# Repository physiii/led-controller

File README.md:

# open-led
ESP32 Based LED Controller

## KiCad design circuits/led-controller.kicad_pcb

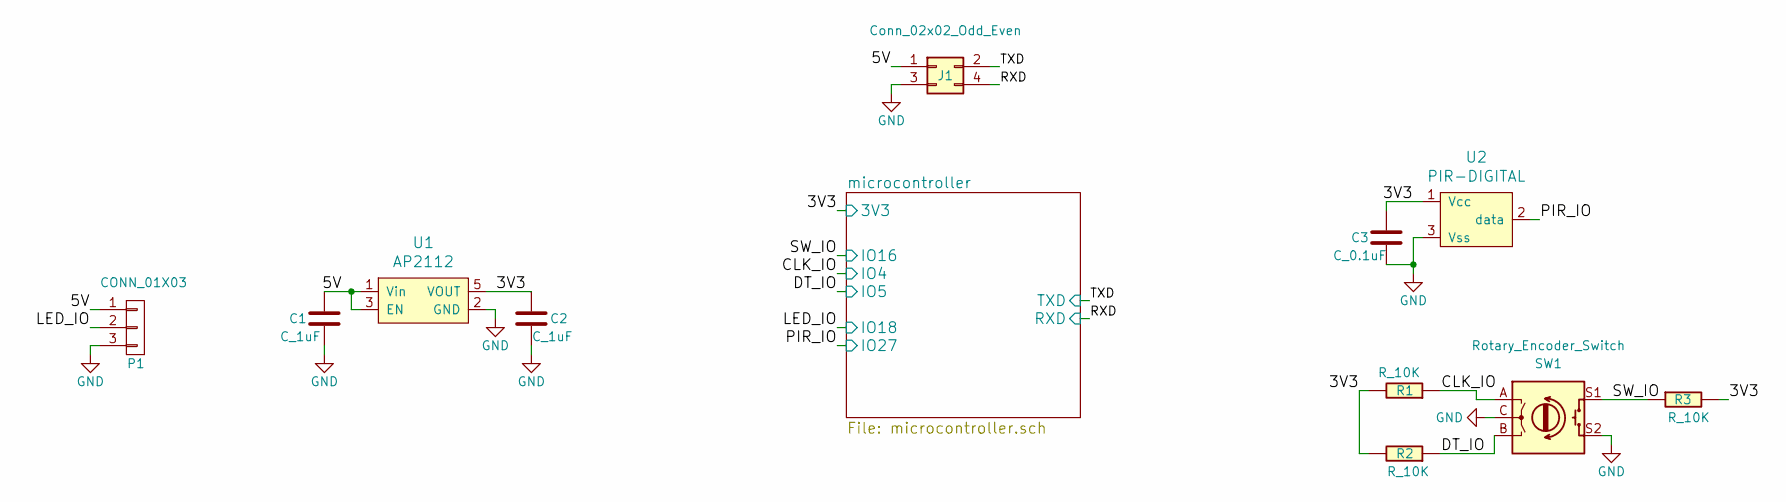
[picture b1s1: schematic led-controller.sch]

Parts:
C1, C2: C_1uF; C_0603_1608Metric_Pad1.05x0.95mm_HandSolder; Part Number GCM188R71C105KA64D
C3: C_0.1uF; C_0603_1608Metric_Pad1.05x0.95mm_HandSolder; Part Number C1608X8R1H104K080AB
J1: Conn_02x02_Odd_Even; PinHeader_2x02_P2.54mm_Vertical_SMD
P1: CONN_01X03; PinHeader_1x03_P2.54mm_Vertical
R1, R2, R3: R_10K; R_0603_1608Metric_Pad1.05x0.95mm_HandSolder; Part Number RC0603JR-0710KL
SW1: Rotary_Encoder_Switch; RotaryEncoder_Alps_EC11E-Switch_Vertical_H20mm; Part Number EC11
U1: AP2112; SOT-23-5_HandSoldering; Part Number AP2112
U2: PIR-DIGITAL; TO-5-3; Part Number PYQ2898

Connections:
/3V3: C2.1, C3.1, R1.2, R2.2, R3.2, U1.5 (VOUT), U2.1 (Vcc); also elsewhere on the board
/5V: C1.1, J1.1, P1.1, U1.1 (Vin), U1.3 (EN)
/CLK_IO: R1.1, SW1.A; also elsewhere on the board
/DT_IO: R2.1, SW1.B; also elsewhere on the board
/LED_IO: P1.2; also elsewhere on the board
/PIR_IO: U2.2 (data); also elsewhere on the board
/RXD: J1.4; also elsewhere on the board
/SW_IO: R3.1, SW1.S1; also elsewhere on the board
/TXD: J1.2; also elsewhere on the board
GND: C1.2, C2.2, C3.2, J1.3, P1.3, SW1.C, SW1.S2, U1.2 (GND), U2.3 (Vss); also elsewhere on the board

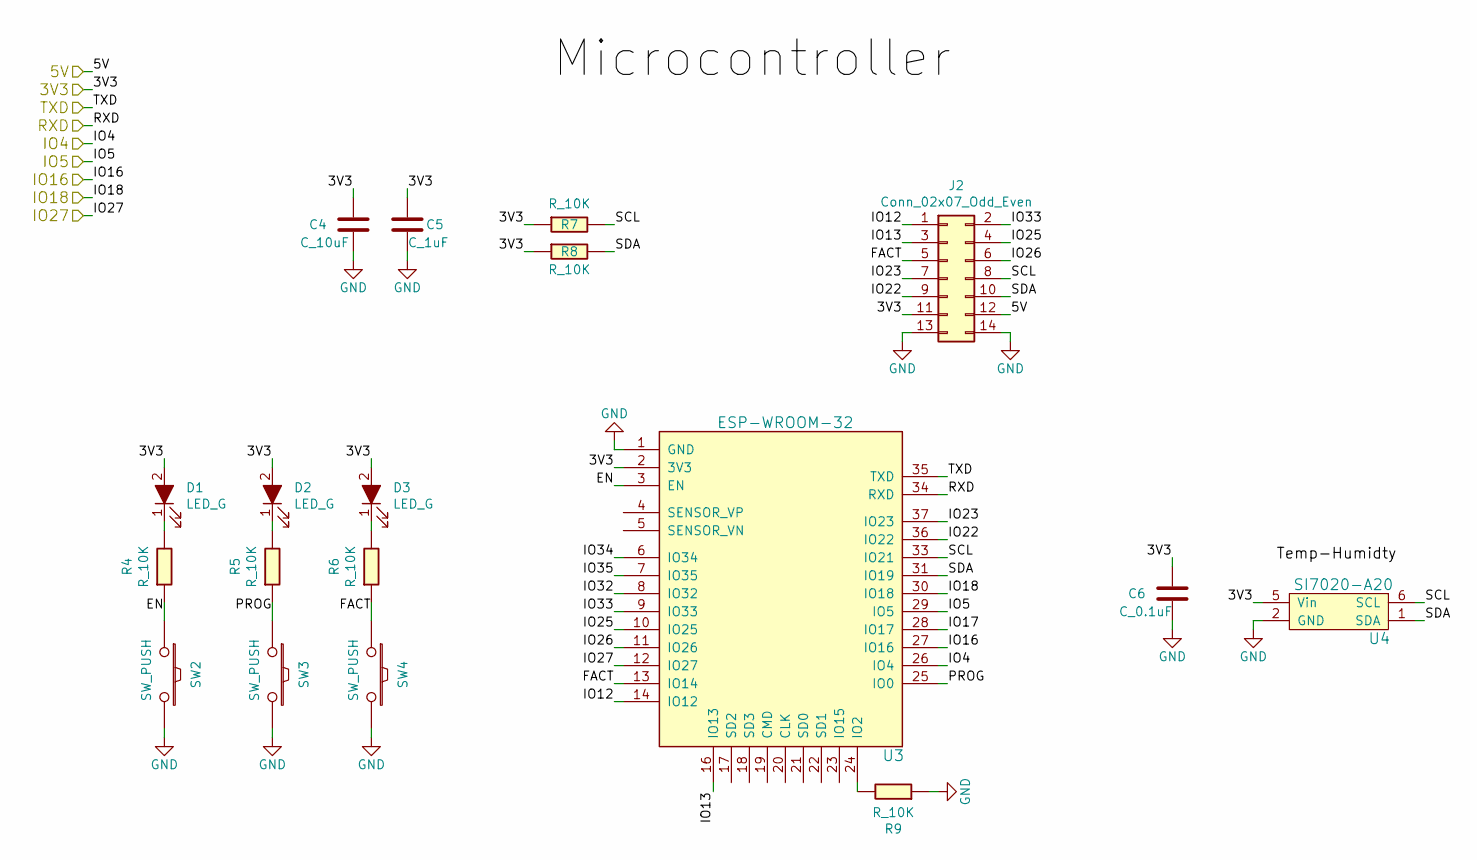
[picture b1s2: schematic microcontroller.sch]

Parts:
C4: C_10uF; C_0603_1608Metric_Pad1.05x0.95mm_HandSolder; Part Number GRM188R61E106KA73D
C5: C_1uF; C_0603_1608Metric_Pad1.05x0.95mm_HandSolder; Part Number GCM188R71C105KA64D
C6: C_0.1uF; C_0603_1608Metric_Pad1.05x0.95mm_HandSolder; Part Number C1608X8R1H104K080AB
D1, D2, D3: LED_G; D_0603_1608Metric_Pad1.05x0.95mm_HandSolder; Part Number 150060VS75000
J2: Conn_02x07_Odd_Even; PinHeader_2x07_P2.54mm_Vertical_SMD
R4, R5, R6, R7, R8, R9: R_10K; R_0603_1608Metric_Pad1.05x0.95mm_HandSolder; Part Number RC0603JR-0710KL
SW2, SW3, SW4: SW_PUSH; SW_Push_1P1T_NO_CK_KMR2; Part Number KMR211NG LFS
U3: ESP-WROOM-32; Part Number ESP-WROOM-32
U4: SI7020-A20; Part Number SI7020-A20-GM1R

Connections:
/3V3: C4.1, C5.1, C6.1, D1.2 (A), D2.2 (A), D3.2 (A), J2.11, R7.1, R8.1, U3.2 (3V3), U4.5 (Vin); also elsewhere on the board
/CLK_IO: U3.26 (IO4); also elsewhere on the board
/DT_IO: U3.29 (IO5); also elsewhere on the board
/LED_IO: U3.30 (IO18); also elsewhere on the board
/PIR_IO: U3.12 (IO27); also elsewhere on the board
/RXD: U3.34 (RXD); also elsewhere on the board
/SW_IO: U3.27 (IO16); also elsewhere on the board
/TXD: U3.35 (TXD); also elsewhere on the board
/microcontroller/5V: J2.12
/microcontroller/EN: R4.1, SW2.1, U3.3 (EN)
/microcontroller/FACT: J2.5, R6.1, SW4.1, U3.13 (IO14)
/microcontroller/IO12: J2.1, U3.14 (IO12)
/microcontroller/IO13: J2.3, U3.16 (IO13)
/microcontroller/IO17: U3.28 (IO17)
/microcontroller/IO22: J2.9, U3.36 (IO22)
/microcontroller/IO23: J2.7, U3.37 (IO23)
/microcontroller/IO25: J2.4, U3.10 (IO25)
/microcontroller/IO26: J2.6, U3.11 (IO26)
/microcontroller/IO32: U3.8 (IO32)
/microcontroller/IO33: J2.2, U3.9 (IO33)
/microcontroller/IO34: U3.6 (IO34)
/microcontroller/IO35: U3.7 (IO35)
/microcontroller/PROG: R5.1, SW3.1, U3.25 (IO0)
/microcontroller/SCL: J2.8, R7.2, U3.33 (IO21), U4.6 (SCL)
/microcontroller/SDA: J2.10, R8.2, U3.31 (IO19), U4.1 (SDA)
GND: C4.2, C5.2, C6.2, J2.13, J2.14, R9.1, SW2.2, SW3.2, SW4.2, U3.1 (GND), U4.2 (GND); also elsewhere on the board
unnamed: D1.1 (K), R4.2
unnamed: D2.1 (K), R5.2
unnamed: D3.1 (K), R6.2
unnamed: R9.2, U3.24 (IO2)

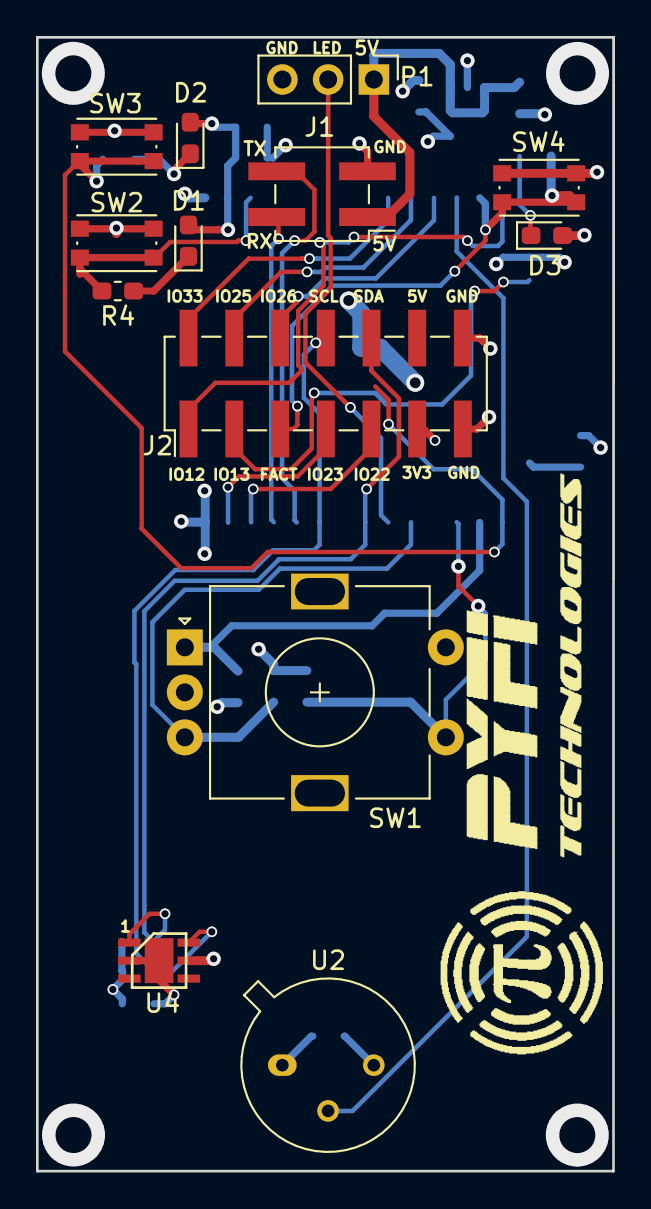
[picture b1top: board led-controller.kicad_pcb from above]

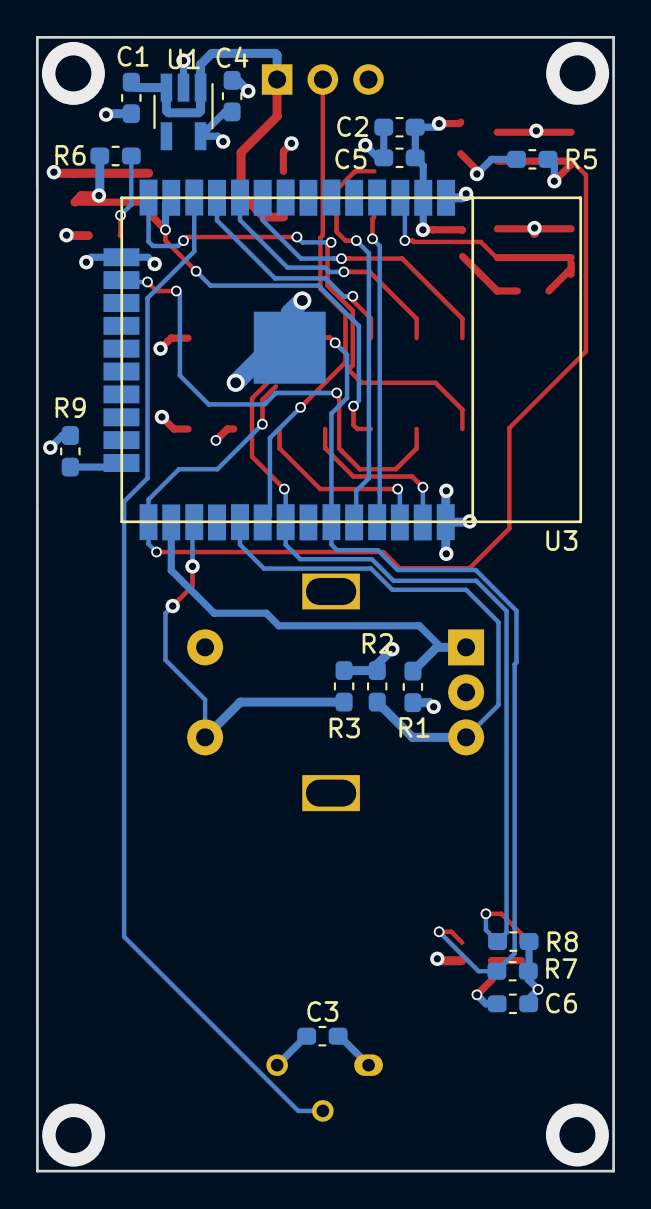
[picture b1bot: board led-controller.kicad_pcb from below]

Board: 4 copper layers, 32.0 x 63.0 mm, 30 parts (16 on the bottom side), 26 nets.

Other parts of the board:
LOGO: LOGO

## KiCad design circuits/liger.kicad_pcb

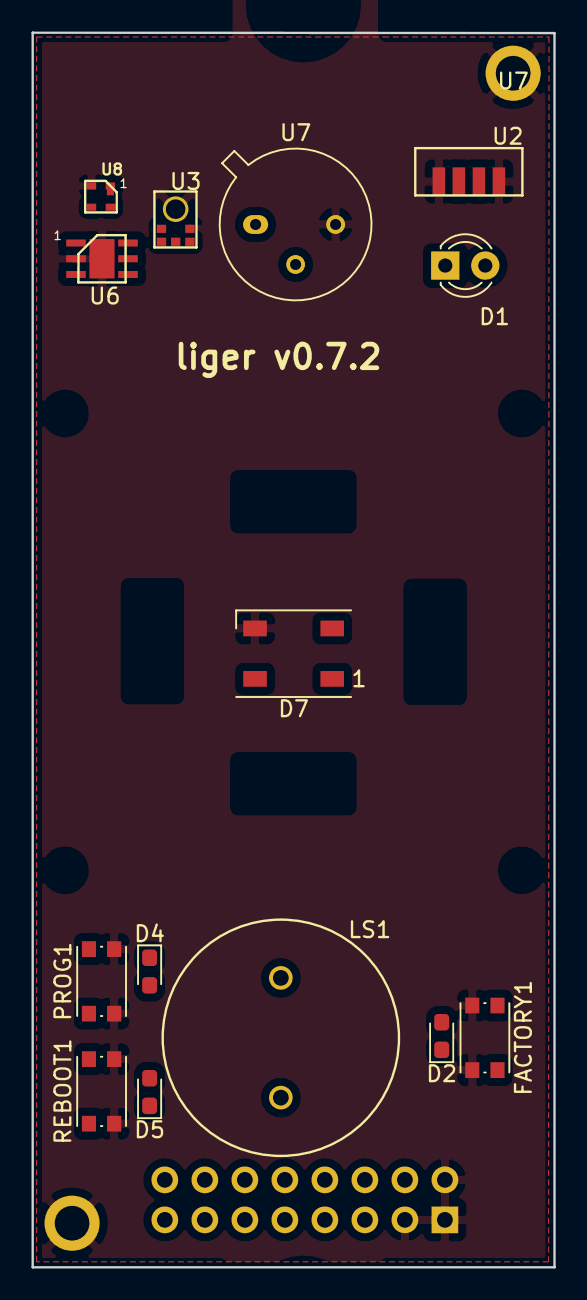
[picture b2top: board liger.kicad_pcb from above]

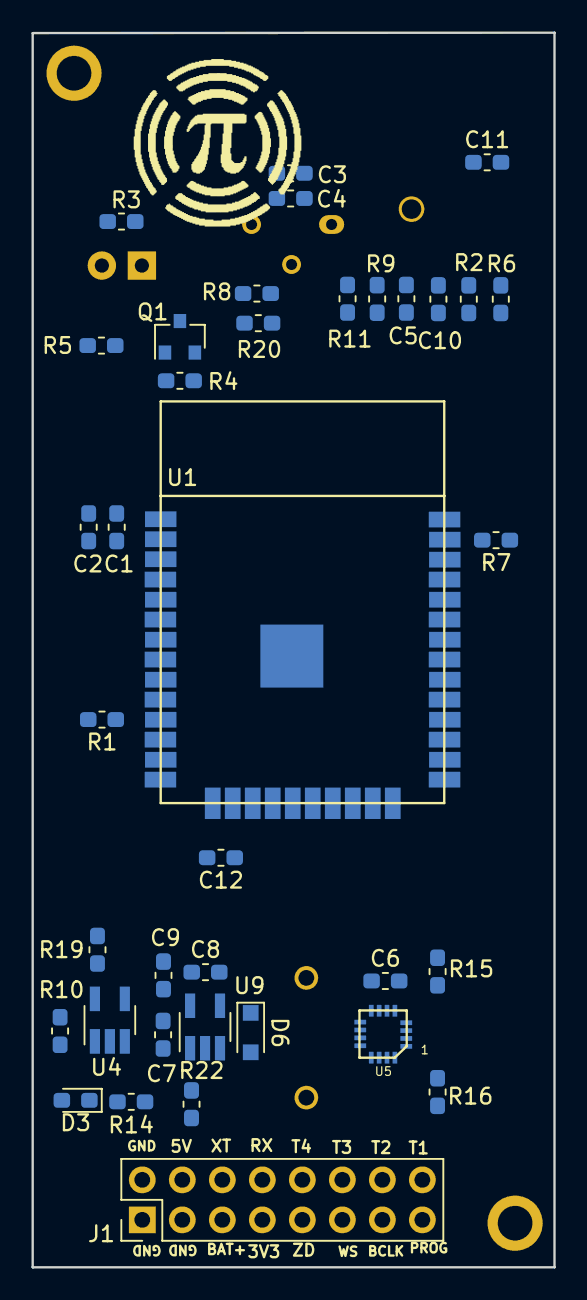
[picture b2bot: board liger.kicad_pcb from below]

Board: 4 copper layers, 33.1 x 78.4 mm, 53 parts (38 on the bottom side), 41 nets, no tracks yet.

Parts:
C1: C_10uF; C_0603_1608Metric_Pad1.05x0.95mm_HandSolder
C2, C7, C8, C9, C12: C_1uF; C_0603_1608Metric_Pad1.05x0.95mm_HandSolder
C3, C5, C6, C10, C11: C_0.1uF; C_0603_1608Metric_Pad1.05x0.95mm_HandSolder
C4: C_100pF; C_0603_1608Metric_Pad1.05x0.95mm_HandSolder
D1: LED; LED_D3.0mm
D2, D3, D4, D5: LED-0603-G; LED_0603_1608Metric_Pad1.05x0.95mm_HandSolder
D6: D_Schottky-BAT20JFILM; D_SOD-323_HandSoldering
D7: WS2812B; LED_WS2812B_PLCC4_5.0x5.0mm_P3.2mm
FACTORY1: SW_PUSH; SW_SPST_KMR2
J1: Conn_02x08_Odd_Even; PinHeader_2x08_P2.54mm_Vertical
LOGO: pyfi_symbol
LS1: speaker-CVS-1508; speaker-1508
PROG1: SW_PUSH; SW_SPST_KMR2
Q1: Q_NPN_BEC; SOT-23
R1, R7, R8, R11: R_47.5; R_0603_1608Metric_Pad1.05x0.95mm_HandSolder
R2, R6, R22: R_10k; R_0603_1608Metric_Pad1.05x0.95mm_HandSolder
R3, R4, R10, R14, R15, R16: R_1k; R_0603_1608Metric_Pad1.05x0.95mm_HandSolder
R5: 36; R_0603_1608Metric_Pad1.05x0.95mm_HandSolder
R9, R20: R_100k; R_0603_1608Metric_Pad1.05x0.95mm_HandSolder
R19: R_2k; R_0603_1608Metric_Pad1.05x0.95mm_HandSolder
REBOOT1: SW_PUSH; SW_SPST_KMR2
U1: ESP-WROOM-32
U2: IR-RX-TSOP34438; TSOP75338TR
U3: SPH0645LM4H-B
U4: MCP73831T; SOT-23-5_HandSoldering
U5: MAX98357AETE+T; MAX98357A
U6: SI7020-A20
U7: PYQ2898; TO-5-3
U7#2: housing-mounts; generic-housing-mounts-md
U8: TSL45315CL; LIGHT-SENSOR-TSL45315CL
U9: AP2112; SOT-23-5_HandSoldering

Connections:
/3V3: C1.1, C2.1, C3.1, C5.1, C8.1, C10.1, C11.1, D2.2, D4.2, D5.2, J1.7, R2.1, R5.1, R6.1, U1.2, U2.Vs, U3.5, U6.5, U7.1, U8.1, U9.5
/BUTTON_LED: D7.4, U1.30
/EN: R16.2, REBOOT1.1, U1.3
/FACTORY_RST: FACTORY1.1, R14.2, U1.13
/I2S_BCLK: J1.13, R1.2, U3.4, U5.16
/I2S_DATA_IN: R11.1, U1.36
/I2S_DATA_OUT: U1.10, U5.1
/I2S_WS: J1.11, R7.1, U3.1, U5.14
/IR_RX: R3.1, U1.27
/IR_TX: R4.2, U1.26
/PIR: R8.1, R20.2, U1.23
/PROG: J1.15, PROG1.1, R15.2, U1.25
/RELAY_1: J1.16, U1.24
/RELAY_2: J1.14, U1.29
/RELAY_3: J1.12, U1.28
/RELAY_4: J1.10, U1.6
/RXD: J1.8, U1.34
/SCL: R2.2, U1.33, U6.6, U8.4
/SDA: R6.2, U1.31, U6.1, U8.3
/TXD: J1.6, U1.35
/V_BAT: C9.1, J1.5, U4.3
/V_IN: C6.1, C7.1, C12.2, D6.1, D7.1, U5.4, U5.7, U9.1, U9.3
/V_USB: D6.2, J1.4, R10.1, R22.1, U4.4
/ZERO_DETECT: J1.9, U1.7
GND: C1.2, C2.2, C3.2, C4.2, C5.2, C6.2, C7.2, C8.2, C9.2, C10.2, C11.2, C12.1, D7.3, FACTORY1.2, J1.1, J1.2, J1.3, PROG1.2, Q1.2, R9.1, R19.1, R20.1, R22.2, REBOOT1.2, U1.1, U2.GND, U3.2, U3.3, U4.2, U5.3, U6.2, U7.3, U7#2.1, U8.2, U9.2
unnamed: C4.1, R8.2, U7.2
unnamed: D1.1, Q1.3
unnamed: D1.2, R5.2
unnamed: D2.1, R14.1
unnamed: D3.1, U4.1
unnamed: D3.2, R10.2
unnamed: D4.1, R15.1
unnamed: D5.1, R16.1
unnamed: LS1.1, U5.10
unnamed: LS1.2, U5.9
unnamed: Q1.1, R4.1
unnamed: R1.1, U1.11
unnamed: R3.2, U2.OUT
unnamed: R7.2, U1.37
unnamed: R9.2, R11.2, U3.6
unnamed: R19.2, U4.5

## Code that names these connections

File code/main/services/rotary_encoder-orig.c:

#include <stdio.h>
#include <string.h>
#include <stdlib.h>
#include "freertos/FreeRTOS.h"
#include "freertos/task.h"
#include "freertos/queue.h"
#include "driver/gpio.h"

#define NR    0 // not rotating
#define CW    1 // clock-wise rotation
#define CCW   2 // counter-clock-wise rotation
#define ESP_INTR_FLAG_DEFAULT 0

int debounce_count = 0;
int hold_thresh = 10;
int hold_cnt = 0;
int rotary_state = 0;
int prev_rotary_state = 0;
bool start_hold_cnt = false;
bool select_mode_enabled = false;

static xQueueHandle gpio_evt_queue = NULL;

struct rotary_encoder {
  int SW;
  int CLK;
  int DT;
  int SW_IO;
  int CLK_IO;
  int DT_IO;
  int rotated;
  int pressed;
  int dt_value;
  int clk_value;
  int prev_dt_value;
  long int debounce;
};

struct rotary_encoder rcA;

static void IRAM_ATTR gpio_isr_handler(void* arg)
{
    uint32_t gpio_num = (uint32_t) arg;
    // xQueueSendFromISR(gpio_evt_queue, &gpio_num, NULL);
    // Rotation event
    if (gpio_num == rcA.DT_IO) {
      rcA.clk_value = gpio_get_level(rcA.CLK_IO);
      rcA.dt_value = gpio_get_level(rcA.DT_IO);
      if (!rcA.dt_value && rcA.prev_dt_value) {
        if (rcA.clk_value) {
          rotary_state = CCW;
        } else {
          rotary_state = CW;
        }
      }
      rcA.prev_dt_value = rcA.dt_value;
    }
}

void reset_hold_count() {
  hold_cnt = 0;
}

void toggle_hold_count() {
  if (start_hold_cnt) {
    printf("double click delay: %d\n", hold_cnt);
  } else {
    hold_cnt = 0;
  }

  start_hold_cnt = !start_hold_cnt;
}

void start_hold_count()
{
  start_hold_cnt = true;
}

void stop_hold_count()
{
  start_hold_cnt = false;
}

int get_click_delay()
{
  int ret = hold_cnt;
  hold_cnt = 0;
  return ret;
}

void enter_scene_select_mode(bool mode)
{
  select_mode_enabled = mode;
  printf("Scene select mode. %d\n", select_mode_enabled);
}

static void rotary_encoder_task(void *pvParameter) {
  while (1) {

    if (rotary_state == CCW) {
      // if (prev_rotary_state != rotary_state) printf("Rotating CCW.\n");
      printf("Rotating CCW.\n");
    }

    if (rotary_state == CW) {
      // if (prev_rotary_state != rotary_state) printf("Rotating CW.\n");
      // nextMode();
      printf("Rotating CW.\n");
    }
    // prev_rotary_state = rotary_state;
    // rcA.prev_dt_value = rcA.dt_value;

    rotary_state = NR;
    vTaskDelay(10 / portTICK_PERIOD_MS);
  }
}

static void rotary_encoder_task_old(void* arg)
{
    uint32_t io_num;
    int cnt = 0;
    for(;;) {
        if(xQueueReceive(gpio_evt_queue, &io_num, portMAX_DELAY)) {
            // printf("GPIO[%d] intr, val: %d\n", io_num, gpio_get_level(io_num));
            cJSON *level_json = NULL;

            // Switch event
            if (io_num == rcA.SW_IO) {
              rcA.pressed = !gpio_get_level(rcA.SW_IO);
              if (!rcA.pressed) continue;
              if (debounce_count - rcA.debounce > 0) {
                LED_payload = cJSON_CreateObject();
                level_json = cJSON_CreateBool(true);
                cJSON_AddItemToObject(LED_payload, "toggle", level_json);
                int delay = get_click_delay();
                printf("Toggle (%d)\n", delay);
                if (delay < 5) {
                  enter_scene_select_mode(true);
                } else {
                  enter_scene_select_mode(false);
                }
                debounce_count = 0;
              }
            }

            // Rotation event
            if (io_num == rcA.DT_IO) {
              rcA.clk_value = gpio_get_level(rcA.CLK_IO);
              rcA.dt_value = gpio_get_level(rcA.DT_IO);

              if (!rcA.dt_value && rcA.prev_dt_value) {
                if (rcA.clk_value) {
                  LED_payload = cJSON_CreateObject();
                  level_json = cJSON_CreateNumber(12);
                  if (select_mode_enabled) {
                    nextMode();
                  } else {
                    cJSON_AddItemToObject(LED_payload, "decBrightness", level_json);
                  }

                  printf("CCW\n");
                } else {
                  LED_payload = cJSON_CreateObject();
                  level_json = cJSON_CreateNumber(12);
                  if (select_mode_enabled) {
                    prevMode();
                  } else {
                    cJSON_AddItemToObject(LED_payload, "incBrightness", level_json);
                  }
                  printf("CW\n");
                }
              }
              rcA.prev_dt_value = rcA.dt_value;
            }

        }
    }
}

static void debounce_task(void *pvParameter) {
  while (1) {
    debounce_count++;
    vTaskDelay(10 / portTICK_PERIOD_MS);
  }
}

static void hold_task(void *pvParameter) {
  while (1) {
    hold_cnt++;
    vTaskDelay(100 / portTICK_PERIOD_MS);
  }
}

void rotary_encoder_main()
{

    rcA.SW_IO = 16;
    rcA.CLK_IO = 4;
    rcA.DT_IO = 5;


    // #define GPIO_INPUT_PIN_SEL  ((1ULL<<SW_A_IO) | (1ULL<<CLK_A_IO) | (1ULL<<DT_A_IO) | (1ULL<<SW_B_IO) | (1ULL<<CLK_B_IO) | (1ULL<<DT_B_IO))
    unsigned long long GPIO_INPUT_PIN_SEL =
      (1ULL<<rcA.SW_IO)
      | (1ULL<<rcA.CLK_IO)
      | (1ULL<<rcA.DT_IO);

    gpio_config_t io_conf;
    io_conf.intr_type = GPIO_PIN_INTR_ANYEDGE;
    io_conf.pin_bit_mask = GPIO_INPUT_PIN_SEL;
    io_conf.mode = GPIO_MODE_INPUT;
    io_conf.pull_up_en = 1;
    gpio_config(&io_conf);

    gpio_evt_queue = xQueueCreate(10, sizeof(uint32_t));
    xTaskCreate(rotary_encoder_task, "rotary_encoder_task", 2048, NULL, 10, NULL);
    xTaskCreate(debounce_task, "debounce_task", 2048, NULL, 10, NULL);
    xTaskCreate(hold_task, "hold_task", 2048, NULL, 10, NULL);

    gpio_install_isr_service(ESP_INTR_FLAG_DEFAULT);

    gpio_isr_handler_add(rcA.SW_IO, gpio_isr_handler, (void*) rcA.SW_IO);
    gpio_isr_handler_add(rcA.CLK_IO, gpio_isr_handler, (void*) rcA.CLK_IO);
    gpio_isr_handler_add(rcA.DT_IO, gpio_isr_handler, (void*) rcA.DT_IO);
}

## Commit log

2019-06-02 init!
2019-06-03 testing panel
2019-06-03 starting rotary encoder driver
2019-07-06 starting up...
2019-07-15 init
2019-07-16 adding sheets
2019-07-19 sent to boardhouse
2019-09-20 working on scene selection
2019-09-21 testing rotary library
2019-09-24 added motion light code, scene selection
2019-09-24 restore led state on reboot
2019-10-03 finished first model, probably should start a model branch :)
2019-10-09 starting next board iteration
2019-10-11 sending new board to boardhouse
2019-10-11 adjustment before sending off
2019-10-22 adding menuconfig items
2019-10-22 fixed bug where state was not being saved after reset
2019-10-22 making off time in minutes instead of seconds
2019-10-22 oops, pushed broken code - fixed
2019-10-23 working on fade task
2019-10-31 model changes for new pcb
2019-11-04 added supports to mount
2019-11-08 shrunk screwhole on mount
2020-06-07 Refactoring.
2020-06-13 Refactored, added themes, tested on new website code
